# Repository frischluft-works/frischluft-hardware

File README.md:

# frischluft.works Hardware
Hardware we created for frischluft.works

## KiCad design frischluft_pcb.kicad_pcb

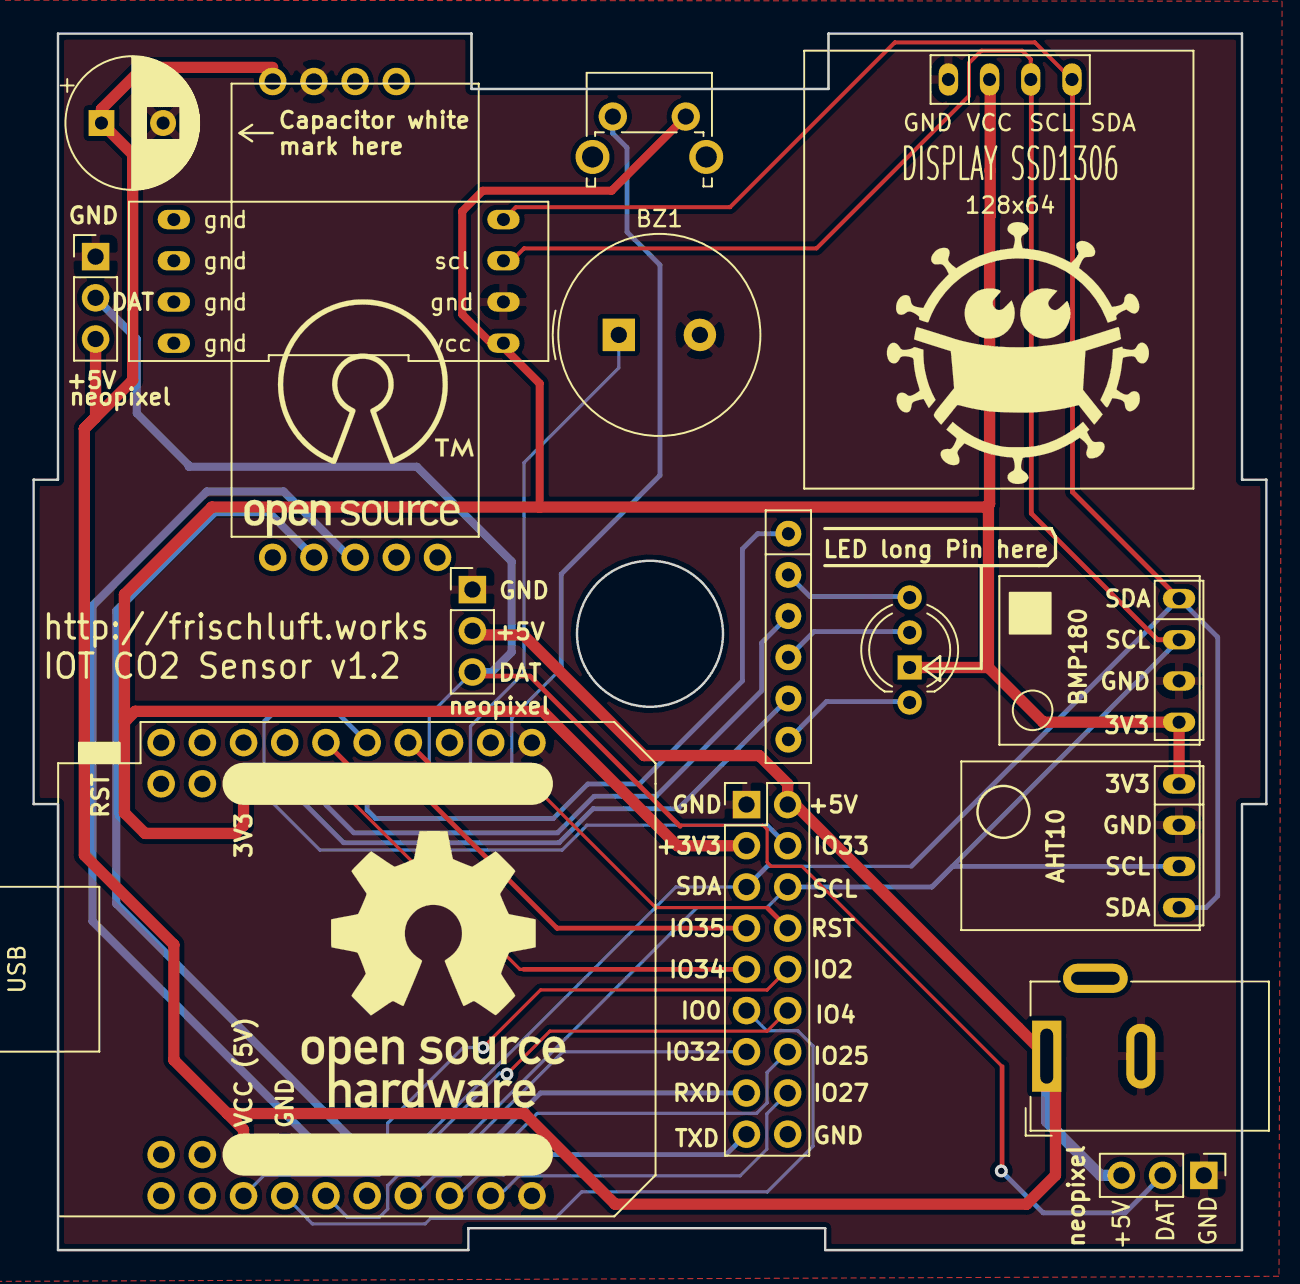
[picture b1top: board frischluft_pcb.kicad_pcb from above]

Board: 2 copper layers, 76.0 x 75.0 mm, 16 parts (0 on the bottom side), 28 nets.

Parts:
BZ1: Buzzer; Buzzer_TDK_PS1240P02BT_D12.2mm_H6.5mm
C1: CP_Small; CP_Radial_D8.0mm_P3.80mm
D1: LED_BRGA; rgb_led_10mm
J1, J2, J5: NEOPIXEL; PinHeader_1x03_P2.54mm_Vertical
J3: connector proto; PinHeader_2x09_P2.54mm_Vertical
J4: SSD 1306 DISPLAY; ssd1306_module
J6: Conn_Coaxial_Power; BarrelJack_Wuerth_6941xx301002
RN1: R_Pack03; R_Array_SIP6_swapped
SW1: SW_Push; SW_Tactile_SPST_Angled_PTS645Vx58-2LFS
U1: mini_esp32; ESP32_flo
U2: bmp180_bob
U3: eht10 bob; aht10-BOB
U4: co2ampel_pcb-rescue_co2ampel_pcb-cache_MH-Z19C-co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; MH-Z19C
U5: SCD40; scd40

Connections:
3V3: D1.4, J3.3, J4.2, SW1.2, U1.16, U2.4, U3.1, U5.1
BUTTON: SW1.1, U1.4
BUZZER: BZ1.1, U1.6
GND: BZ1.2, C1.2, J1.1, J2.1, J3.1, J4.1, J5.1, J6.2, U1.1, U1.22, U1.33, U2.3, U3.2, U4.7, U5.2
LED_B: RN1.3, U1.14
LED_G: RN1.2, U1.12
LED_R: RN1.1, U1.10
NEOPIXEL: J1.3, J2.2, J5.2, U1.8
unnamed: D1.1, RN1.4
unnamed: D1.2, RN1.6
unnamed: D1.3, RN1.5
RX: U1.29, U4.2
SCL: J3.6, J4.3, U1.25, U2.2, U3.3, U5.3
SDA: J3.5, J4.4, U1.27, U2.1, U3.4, U5.4
TX: U1.31, U4.3
VCC: C1.1, J1.2, J2.3, J3.2, J5.3, J6.1, U1.35, U4.6
io_0: J3.11, U1.34
io_2: J3.10, U1.36
io_4: J3.12, U1.32
io_25: J3.14, U1.26
io_27: J3.16, U1.24
io_32: J3.13, U1.28
io_33: J3.4, U1.9
io_34: J3.9, U1.11
io_35: J3.7, U1.7
rst: J3.8, U1.2
rxd: J3.15, U1.23
txd: J3.17, U1.21

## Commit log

2021-05-23 kit hardware v1.3
